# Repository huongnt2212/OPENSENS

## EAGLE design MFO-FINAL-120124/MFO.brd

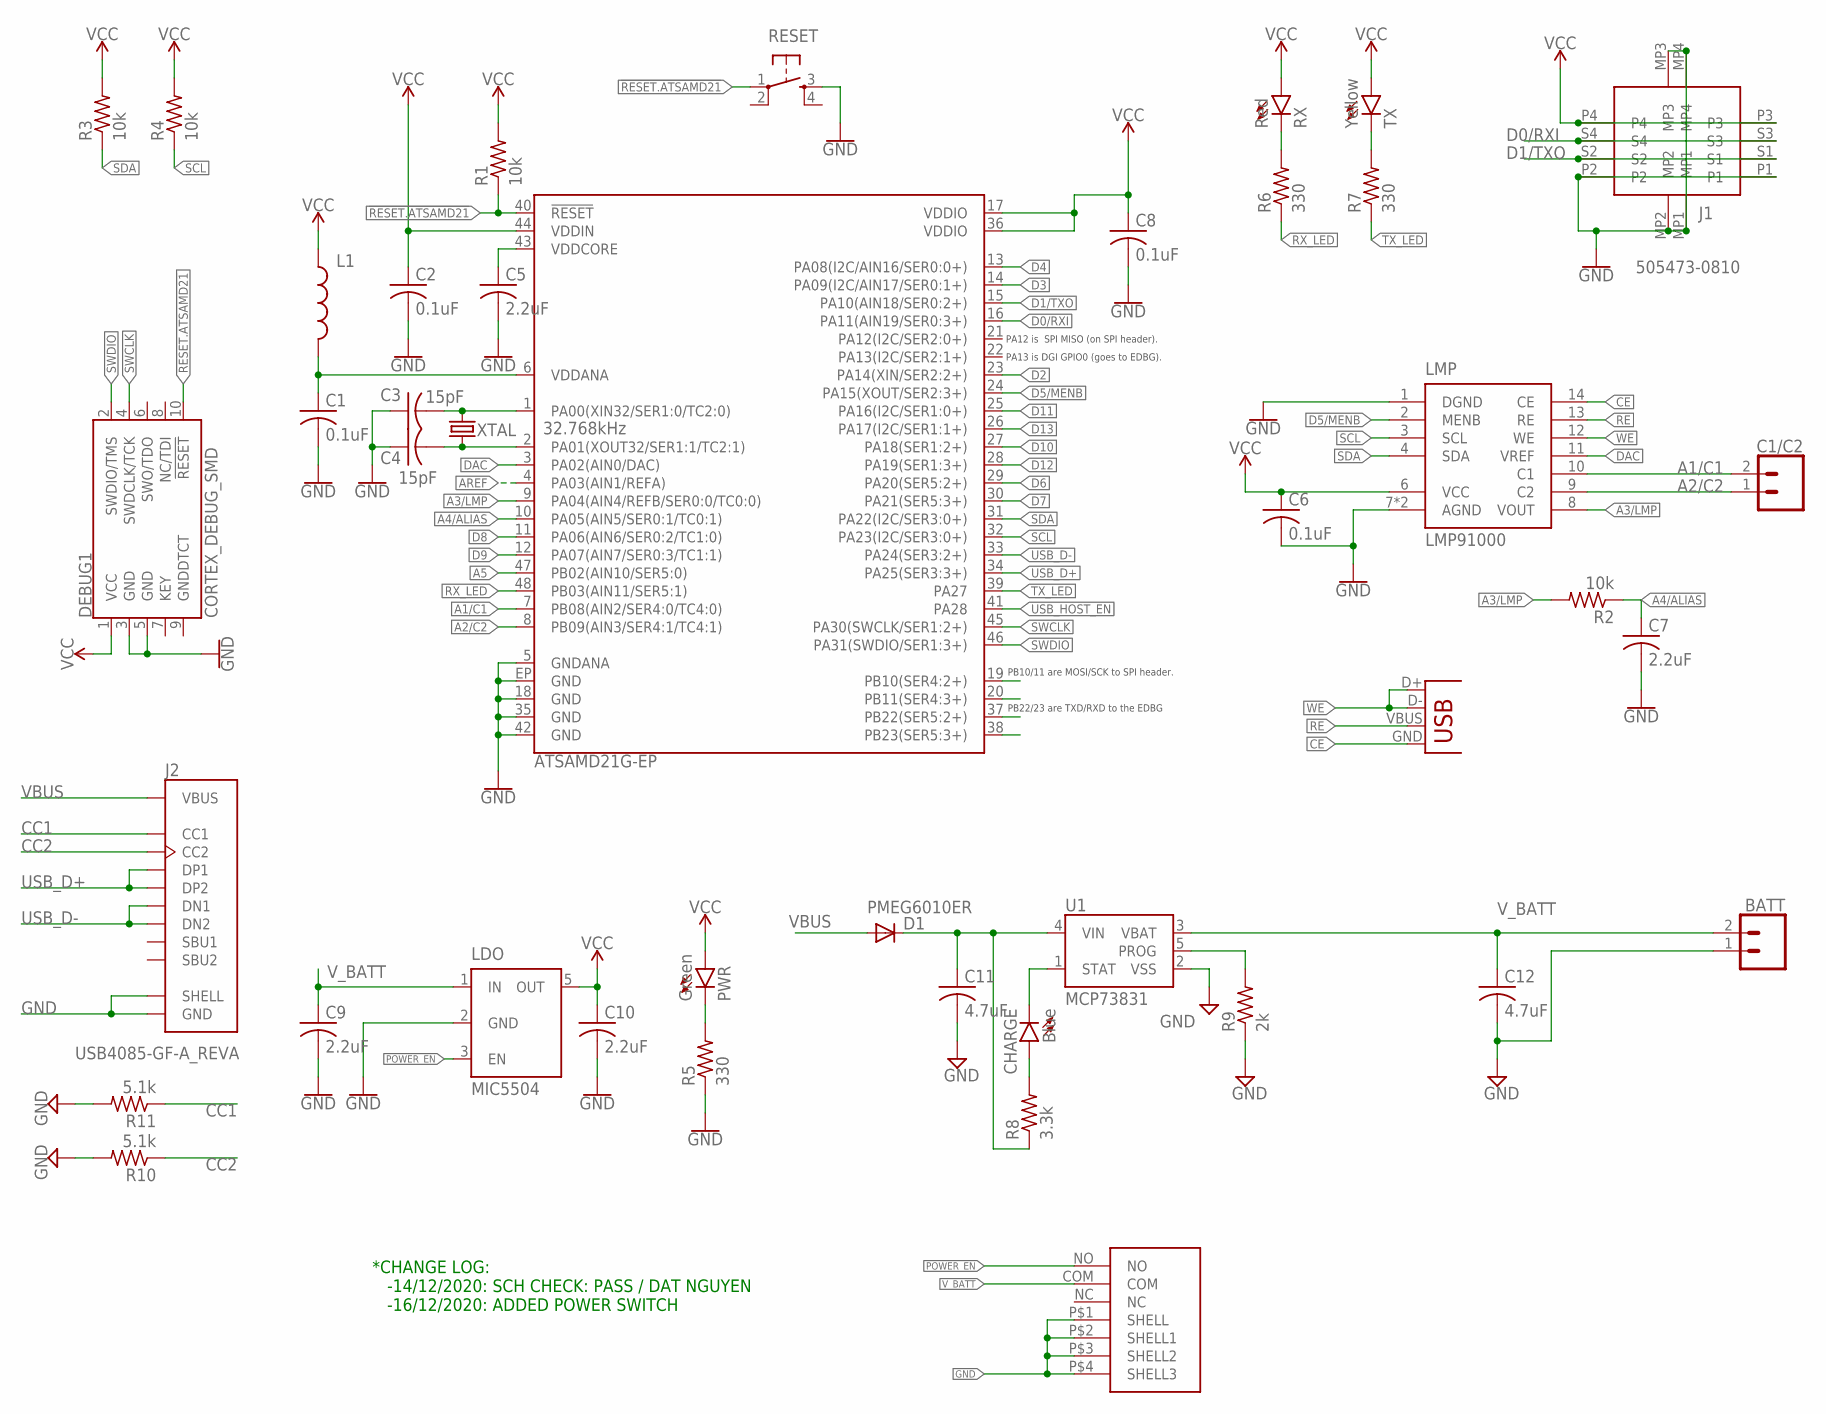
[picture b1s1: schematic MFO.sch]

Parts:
ARDUINO: ATSAMD21G-EP; QFN-48
BATT: CONN_02; 1X02
C1, C2, C6, C8: 0.1uF; C0603
C1/C2: CONN_02; 1X02
C3, C4: 15pF; C0603
C5, C7, C9, C10: 2.2uF; C0603
C11, C12: 4.7uF; C0603
CHARGE: Blue; CHIP-LED0805
D1: PMEG6010ER; DIODE_SOD123
DEBUG1: CORTEX_DEBUG_SMD; SAMTECH_FTSH-105-01
J1: 505473-0810; 5054730810
J2: USB4085-GF-A_REVA; GCT_USB4085-GF-A_REVA
L1: FB - 30Ohm; L0603
LDO: MIC5504; SOT23-5
LMP: LMP91000; WSON-14
PWR: Green; CHIP-LED0805
R1, R2, R3, R4: 10k; R0603
R5, R6, R7: 330; R0603
R8: 3.3k; R0603
R9: 2k; R0603
R10, R11: 5.1k; R0603
RESET: SPST-PTS830GG140; BUTTON-GULLWING
RX: Red; CHIP-LED0805
TX: Yellow; CHIP-LED0805
U1: MCP73831; SOT23-5
U$1: MSK-12C02SMD
X1: USB-A-H
XTAL: 32.768kHz; 2-SMD.NOLEAD.1.2MMTO1.0MM

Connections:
!RESET.ATSAMD21: ARDUINO.40 (!RESET!), DEBUG1.10 (!RESET), R1.1, RESET.1
A1/C1: ARDUINO.7 (PB08(AIN2/SER4:0/TC4:0)), C1/C2.2, LMP.10 (C1)
A2/C2: ARDUINO.8 (PB09(AIN3/SER4:1/TC4:1)), C1/C2.1, LMP.9 (C2)
A3/LMP: ARDUINO.9 (PA04(AIN4/REFB/SER0:0/TC0:0)), LMP.8 (VOUT), R2.2
A4/ALIAS: ARDUINO.10 (PA05(AIN5/SER0:1/TC0:1)), C7.1, R2.1
A5: ARDUINO.47 (PB02(AIN10/SER5:0))
AREF: ARDUINO.4 (PA03(AIN1/REFA))
CC1: J2.A5 (CC1), R11.1
CC2: J2.B5 (CC2), R10.1
CE: LMP.14 (CE), X1.GND
D0/RXI: ARDUINO.16 (PA11(AIN19/SER0:3+)), J1.S3, J1.S4
D1/TXO: ARDUINO.15 (PA10(AIN18/SER0:2+)), J1.S1, J1.S2
D2: ARDUINO.23 (PA14(XIN/SER2:2+))
D3: ARDUINO.14 (PA09(I2C/AIN17/SER0:1+))
D4: ARDUINO.13 (PA08(I2C/AIN16/SER0:0+))
D5/MENB: ARDUINO.24 (PA15(XOUT/SER2:3+)), LMP.2 (MENB)
D6: ARDUINO.29 (PA20(SER5:2+))
D7: ARDUINO.30 (PA21(SER5:3+))
D8: ARDUINO.11 (PA06(AIN6/SER0:2/TC1:0))
D9: ARDUINO.12 (PA07(AIN7/SER0:3/TC1:1))
D10: ARDUINO.27 (PA18(SER1:2+))
D11: ARDUINO.25 (PA16(I2C/SER1:0+))
D12: ARDUINO.28 (PA19(SER1:3+))
D13: ARDUINO.26 (PA17(I2C/SER1:1+))
DAC: ARDUINO.3 (PA02(AIN0/DAC)), LMP.11 (VREF)
GND: ARDUINO.5 (GNDANA), ARDUINO.18 (GND), ARDUINO.35 (GND), ARDUINO.42 (GND), ARDUINO.EP (GND), BATT.1, C1.2, C2.2, C3.1, C4.1, C5.2, C6.2, C7.2, C8.2, C9.2, C10.2, C11.2, C12.2, DEBUG1.3 (GND), DEBUG1.5 (GND), J1.MP1, J1.MP2, J1.MP3, J1.MP4, J1.P1, J1.P2, J2.A1 (GND), J2.A12 (GND), J2.B1 (GND), J2.B12 (GND), J2.P1 (SHELL), J2.P2 (SHELL), J2.P3 (SHELL), J2.P4 (SHELL), LDO.2 (GND), LMP.1 (DGND), LMP.7 (AGND), LMP.DAP (AGND), R5.1, R9.1, R10.2, R11.2, RESET.3, U1.2 (VSS), U$1.P$1 (SHELL), U$1.P$2 (SHELL1), U$1.P$3 (SHELL2), U$1.P$4 (SHELL3)
unnamed: R6.2, RX.C
unnamed: R7.2, TX.C
unnamed: PWR.C, R5.2
unnamed: R9.2, U1.5 (PROG)
unnamed: CHARGE.C, U1.1 (STAT)
unnamed: CHARGE.A, R8.2
unnamed: ARDUINO.1 (PA00(XIN32/SER1:0/TC2:0)), C3.2, XTAL.P$2 (2)
unnamed: ARDUINO.2 (PA01(XOUT32/SER1:1/TC2:1)), C4.2, XTAL.P$1 (1)
POWER_EN: LDO.3 (EN), U$1.NO
RE: LMP.13 (RE), X1.VBUS
RX_LED: ARDUINO.48 (PB03(AIN11/SER5:1)), R6.1
SCL: ARDUINO.32 (PA23(I2C/SER3:0+)), LMP.3 (SCL), R4.1
SDA: ARDUINO.31 (PA22(I2C/SER3:0+)), LMP.4 (SDA), R3.1
SWCLK: ARDUINO.45 (PA30(SWCLK/SER1:2+)), DEBUG1.4 (SWDCLK/TCK)
SWDIO: ARDUINO.46 (PA31(SWDIO/SER1:3+)), DEBUG1.2 (SWDIO/TMS)
TX_LED: ARDUINO.39 (PA27), R7.1
USB_D+: ARDUINO.34 (PA25(SER3:3+)), J2.A6 (DP1), J2.B6 (DP2)
USB_D-: ARDUINO.33 (PA24(SER3:2+)), J2.A7 (DN1), J2.B7 (DN2)
USB_HOST_EN: ARDUINO.41 (PA28)
VBUS: D1.A, J2.A4 (VBUS), J2.A9 (VBUS), J2.B4 (VBUS), J2.B9 (VBUS)
VCC: ARDUINO.17 (VDDIO), ARDUINO.36 (VDDIO), ARDUINO.44 (VDDIN), C2.1, C6.1, C8.1, C10.1, DEBUG1.1 (VCC), J1.P3, J1.P4, L1.1, LDO.5 (OUT), LMP.6 (VCC), PWR.A, R1.2, R3.2, R4.2, RX.A, TX.A
VDDANA1: ARDUINO.6 (VDDANA), C1.1, L1.2
VDDCORE1: ARDUINO.43 (VDDCORE), C5.1
VUSB: C11.1, D1.C, R8.1, U1.4 (VIN)
V_BATT: BATT.2, C9.1, C12.1, LDO.1 (IN), U1.3 (VBAT), U$1.COM
WE: LMP.12 (WE), X1.D+, X1.D-

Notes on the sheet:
PB22/23 are TXD/RXD to the EDBG
PB10/11 are MOSI/SCK to SPI header.
PA12 is SPI MISO (on SPI header).
PA13 is DGI GPIO0 (goes to EDBG).
*CHANGE LOG: -14/12/2020: SCH CHECK: PASS / DAT NGUYEN -16/12/2020: ADDED POWER SWITCH

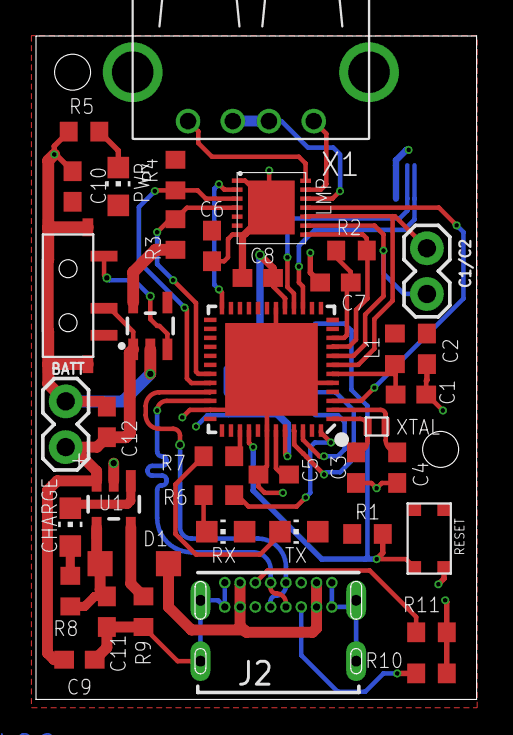
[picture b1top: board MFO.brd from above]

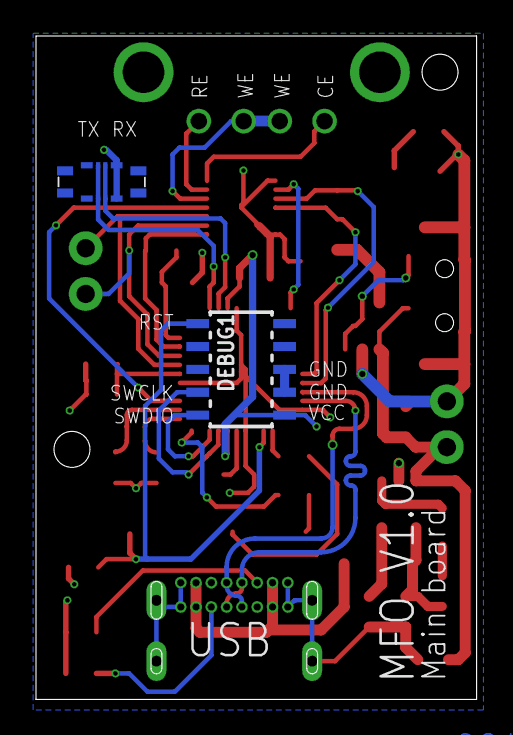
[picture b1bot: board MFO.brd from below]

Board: 2 copper layers, 24.5 x 36.9 mm, 42 parts (2 on the bottom side), 38 nets.
